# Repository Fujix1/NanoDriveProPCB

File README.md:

# NanoDriveProPCB
This is a PCB design repository for NanoDrive PRO

<br />この 作品 は <a rel="license" href="http://creativecommons.org/licenses/by-nc-sa/4.0/">クリエイティブ・コモンズ 表示 - 非営利 - 継承 4.0 国際 ライセンス</a>の下に提供されています。

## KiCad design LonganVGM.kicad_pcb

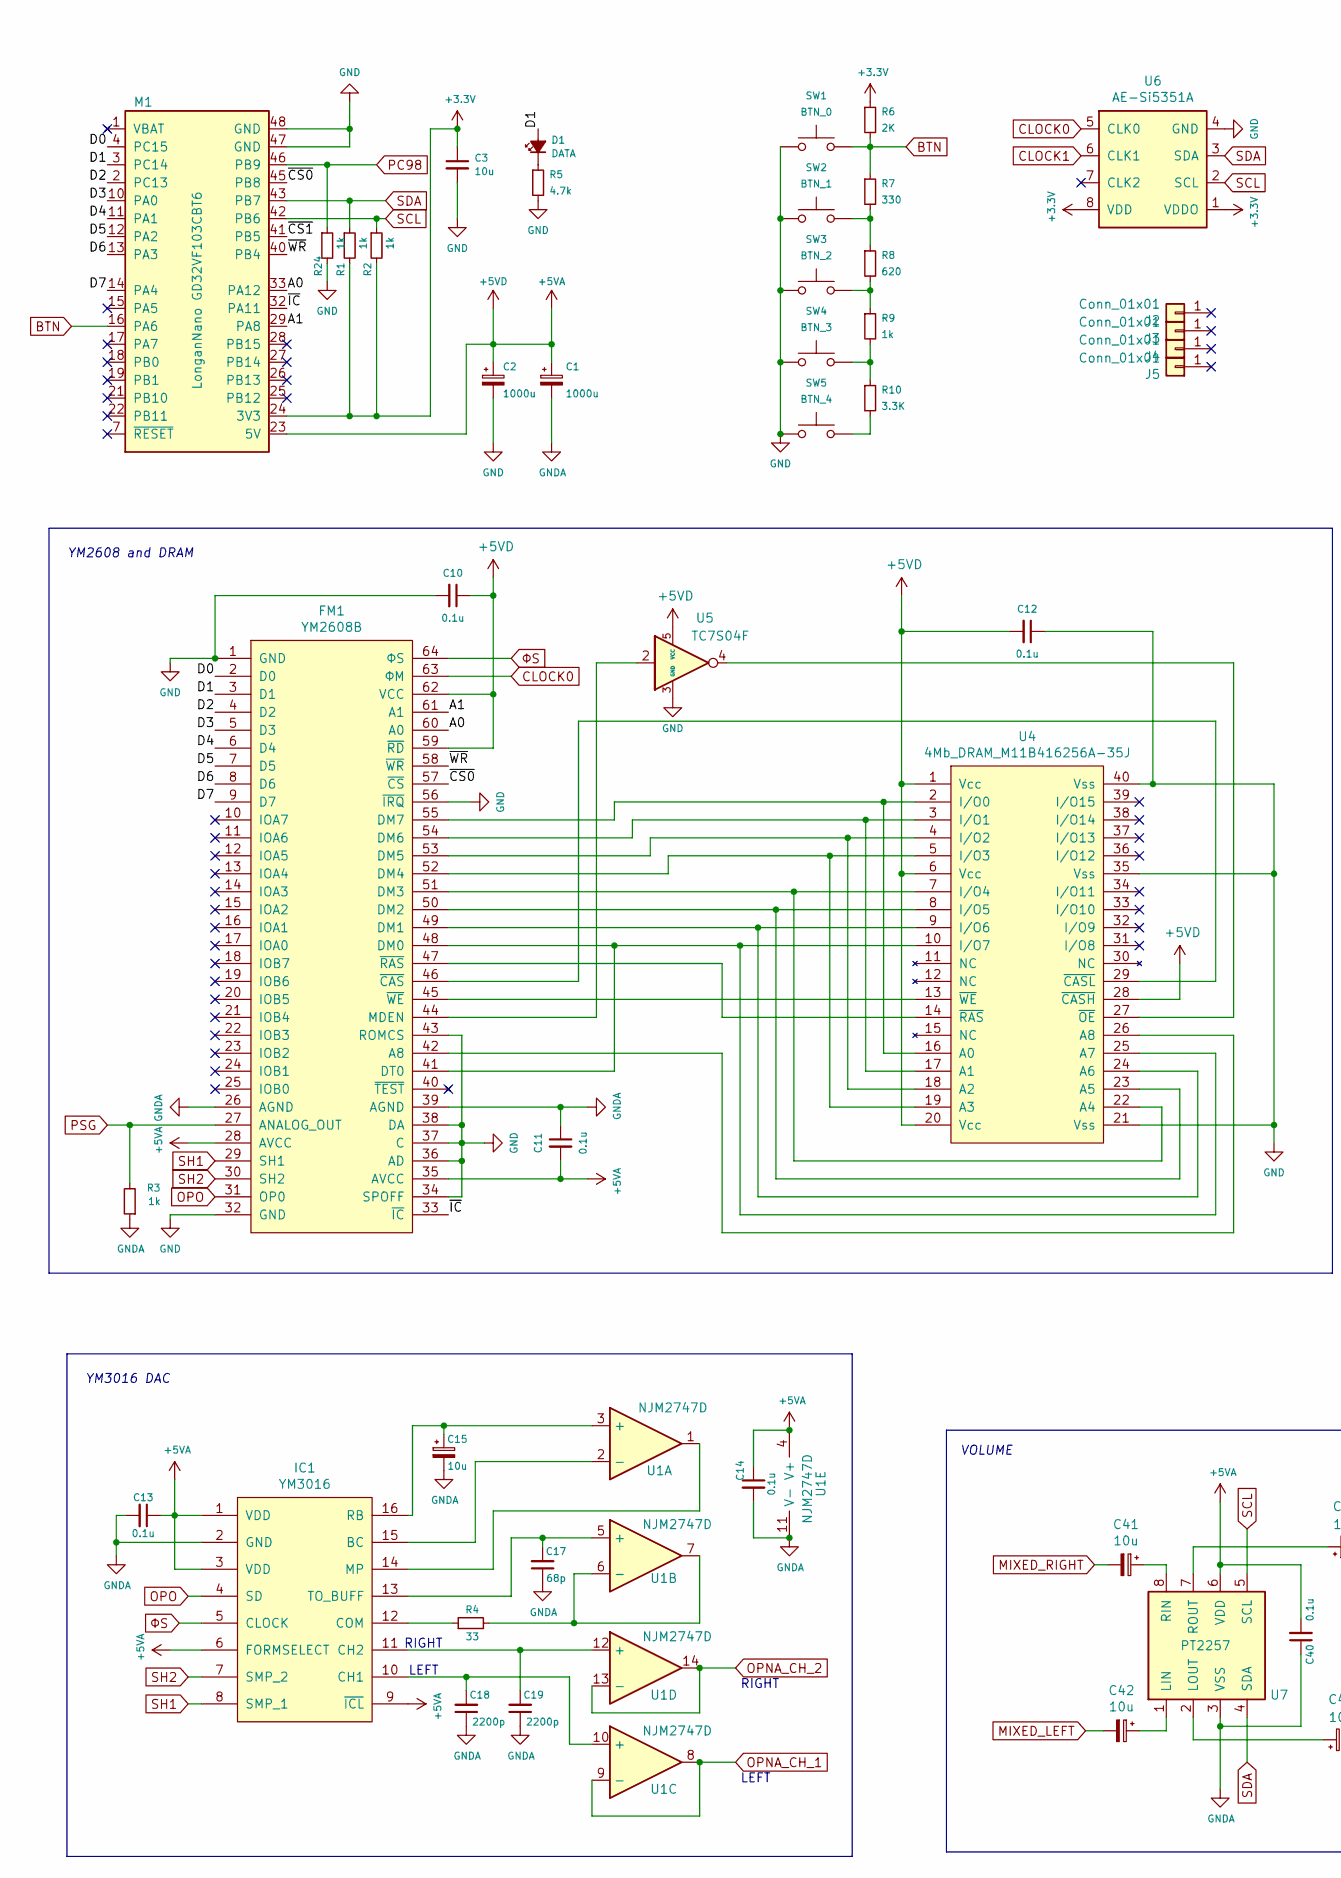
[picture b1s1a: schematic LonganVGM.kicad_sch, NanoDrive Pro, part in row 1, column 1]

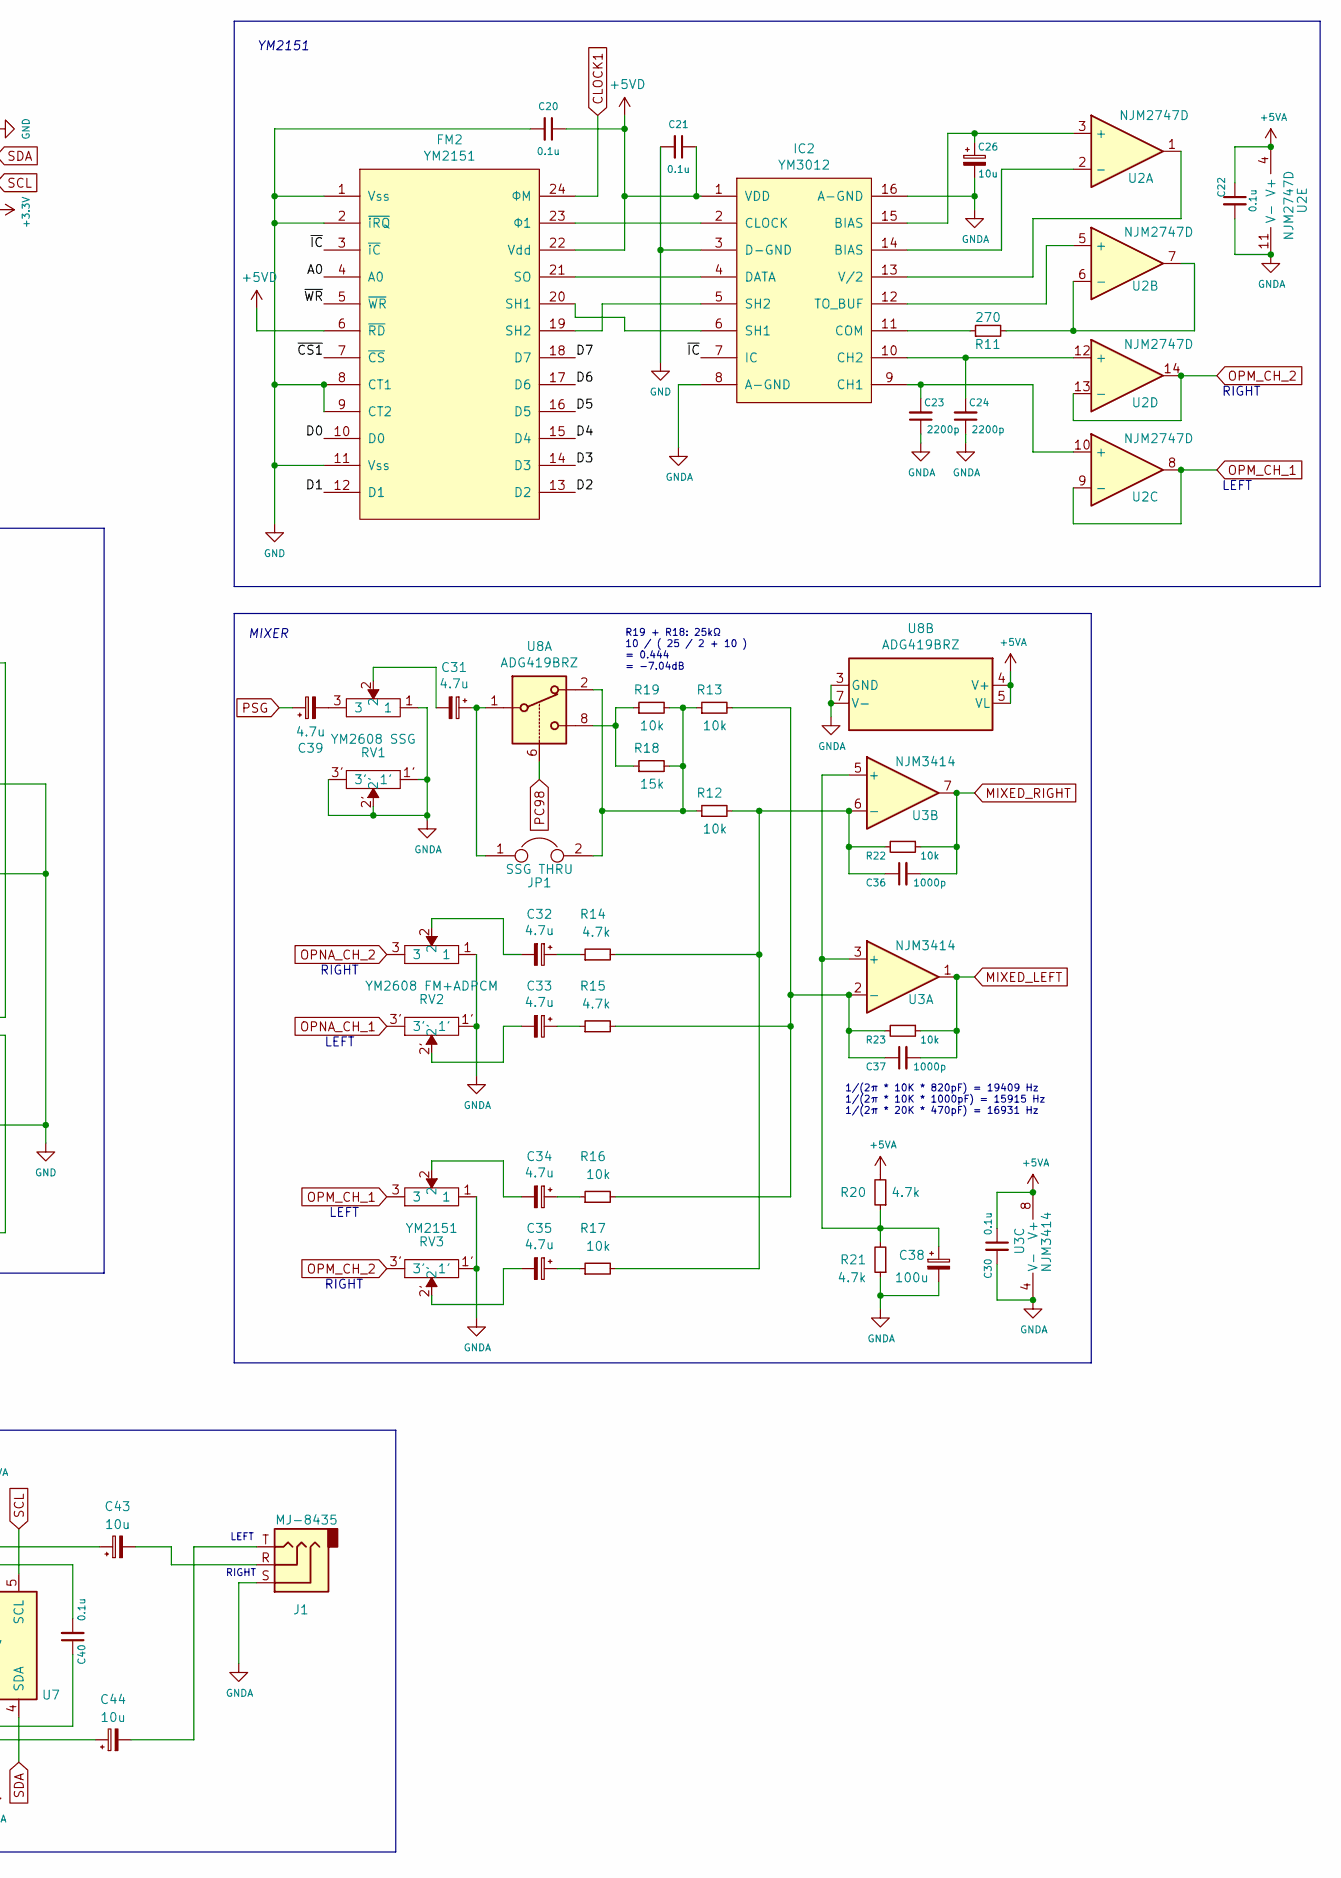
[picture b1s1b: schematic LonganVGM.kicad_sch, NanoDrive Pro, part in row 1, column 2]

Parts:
C1, C2: 1000u; CP_Radial_D8.0mm_P3.50mm
C3, C15, C26, C41, C42, C43, C44: 10u; CP_Radial_D5.0mm_P2.00mm
C10, C11, C12, C13, C14, C20, C21, C22, C30, C40: 0.1u; C_Disc_D4.3mm_W1.9mm_P5.00mm
C17: 68p; C_Disc_D4.3mm_W1.9mm_P5.00mm
C18, C19, C23, C24: 2200p; C_Disc_D4.3mm_W1.9mm_P5.00mm
C31, C32, C33, C34, C35, C39: 4.7u; CP_Radial_D5.0mm_P2.00mm
C36, C37: 1000p; C_Disc_D4.3mm_W1.9mm_P5.00mm
C38: 100u; CP_Radial_D6.3mm_P2.50mm
D1: DATA; LED_Rectangular_W5.0mm_H2.0mm
FM1: YM2608B; SDIP-64
FM2: YM2151; DIP-24_W15.24mm_Socket
IC1: YM3016; DIP-16_W7.62mm_Socket
IC2: YM3012; DIP-16_W7.62mm_Socket
J1: MJ-8435; MJ8435
J2, J3, J4, J5: Conn_01x01; hole
JP1: SSG THRU; PinHeader_1x02_P2.54mm_Vertical
M1: LonganNano GD32VF103CBT6; LonganNano
R1, R2, R3, R9, R24: 1k; R_Axial_DIN0207_L6.3mm_D2.5mm_P7.62mm_Horizontal
R4: 33; R_Axial_DIN0207_L6.3mm_D2.5mm_P7.62mm_Horizontal
R5, R14, R15, R20, R21: 4.7k; R_Axial_DIN0207_L6.3mm_D2.5mm_P7.62mm_Horizontal
R6: 2K; R_Axial_DIN0207_L6.3mm_D2.5mm_P7.62mm_Horizontal
R7: 330; R_Axial_DIN0207_L6.3mm_D2.5mm_P7.62mm_Horizontal
R8: 620; R_Axial_DIN0207_L6.3mm_D2.5mm_P7.62mm_Horizontal
R10: 3.3K; R_Axial_DIN0207_L6.3mm_D2.5mm_P7.62mm_Horizontal
R11: 270; R_Axial_DIN0207_L6.3mm_D2.5mm_P7.62mm_Horizontal
R12, R13, R16, R17, R19, R22, R23: 10k; R_Axial_DIN0207_L6.3mm_D2.5mm_P7.62mm_Horizontal
R18: 15k; R_Axial_DIN0207_L6.3mm_D2.5mm_P7.62mm_Horizontal
RV1: YM2608 SSG; RK12L
RV2: YM2608 FM+ADPCM; RK12L
RV3: YM2151; RK12L
SW1: BTN_0; SW_PUSH_6mm_H4.3mm
SW2: BTN_1; SW_PUSH_6mm_H4.3mm
SW3: BTN_2; SW_PUSH_6mm_H4.3mm
SW4: BTN_3; SW_PUSH_6mm_H4.3mm
SW5: BTN_4; SW_PUSH_6mm_H4.3mm
U1, U2: NJM2747D; DIP-14_W7.62mm_Socket
U3: NJM3414; DIP-8_W7.62mm_Socket
U4: 4Mb_DRAM_M11B416256A-35J; SOP-40
U5: TC7S04F; SOT-23-5_HandSoldering
U6: AE-Si5351A; DIP-8_W7.62mm_Socket
U7: PT2257; DIP-8_W7.62mm_Socket
U8: ADG419BRZ; SO-8_3.9x4.9mm_P1.27mm_handsolder

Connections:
+3V3: C3.1, M1.24 (3V3), R1.2, R2.2, R6.1, U6.1 (VDDO), U6.8 (VDD)
+5VA: C1.1, C2.1, C10.1, C11.2, C12.2, C13.1, C14.1, C20.1, C21.1, C22.1, C30.1, C40.2, FM1.28 (AVCC), FM1.35 (AVCC), FM1.59 (~RD), FM1.62 (VCC), FM2.6 (~RD), FM2.22 (Vdd), IC1.1 (VDD), IC1.3 (VDD), IC1.6 (FORMSELECT), IC1.9 (~ICL), IC2.1 (VDD), M1.23 (5V), R20.2, U1.4 (V+), U2.4 (V+), U3.8 (V+), U4.1 (Vcc), U4.6 (Vcc), U4.20 (Vcc), U4.28 (~CASH), U5.5 (VCC), U7.6 (VDD), U8.4 (V+), U8.5 (VL)
/A0: FM1.60 (A0), FM2.4 (A0), M1.33 (PA12)
/A1: FM1.61 (A1), M1.29 (PA8)
/D0: FM1.2 (D0), FM2.10 (D0), M1.4 (PC15)
/D1: D1.2 (A), FM1.3 (D1), FM2.12 (D1), M1.3 (PC14)
/D2: FM1.4 (D2), FM2.13 (D2), M1.2 (PC13)
/D3: FM1.5 (D3), FM2.14 (D3), M1.10 (PA0)
/D4: FM1.6 (D4), FM2.15 (D4), M1.11 (PA1)
/D5: FM1.7 (D5), FM2.16 (D5), M1.12 (PA2)
/D6: FM1.8 (D6), FM2.17 (D6), M1.13 (PA3)
/D7: FM1.9 (D7), FM2.18 (D7), M1.14 (PA4)
/~CS0: FM1.57 (~CS), M1.45 (PB8)
/~CS1: FM2.7 (~CS), M1.41 (PB5)
/~IC: FM1.33 (~IC), FM2.3 (~iC), IC2.7 (IC), M1.32 (PA11)
/~WR: FM1.58 (~WR), FM2.5 (~WR), M1.40 (PB4)
BTN: M1.16 (PA6), R6.2, R7.1, SW1.2
CLOCK0: FM1.63 (ΦM), U6.5 (CLK0)
CLOCK1: FM2.24 (ΦM), U6.6 (CLK1)
MIXED_LEFT: C37.2, C42.2, R23.1, U3.1
MIXED_RIGHT: C36.2, C41.2, R22.1, U3.7
unnamed: C15.1, IC1.16 (RB), U1.3 (+)
unnamed: C17.2, IC1.13 (TO_BUFF), U1.5 (+)
unnamed: C18.2, IC1.10 (CH1), U1.10 (+)
unnamed: C19.2, IC1.11 (CH2), U1.12 (+)
unnamed: C23.2, IC2.9 (CH1), U2.10 (+)
unnamed: C24.2, IC2.10 (CH2), U2.12 (+)
unnamed: C26.1, IC2.15 (BIAS), U2.3 (+)
unnamed: C31.1, JP1.1, U8.1
unnamed: C31.2, RV1.2
unnamed: C32.1, R14.1
unnamed: C32.2, RV2.2
unnamed: C33.1, R15.1
unnamed: C33.2, RV2.2'
unnamed: C34.1, R16.1
unnamed: C34.2, RV3.2
unnamed: C35.1, R17.1
unnamed: C35.2, RV3.2'
unnamed: C36.1, R12.2, R14.2, R17.2, R22.2, U3.6 (-)
unnamed: C37.1, R13.2, R15.2, R16.2, R23.2, U3.2 (-)
unnamed: C38.1, R20.1, R21.2, U3.3 (+), U3.5 (+)
unnamed: C39.2, RV1.3
unnamed: C41.1, U7.8 (RIN)
unnamed: C42.1, U7.1 (LIN)
unnamed: C43.1, U7.7 (ROUT)
unnamed: C43.2, J1.R
unnamed: C44.1, U7.2 (LOUT)
unnamed: C44.2, J1.T
unnamed: D1.1 (K), R5.1
unnamed: FM1.41 (DT0), FM1.48 (DM0), U4.10 (I/O7), U4.25 (A7)
unnamed: FM1.42 (A8), U4.26 (A8)
unnamed: FM1.44 (MDEN), U5.2
unnamed: FM1.45 (~WE), U4.13 (~WE)
unnamed: FM1.46 (~CAS), U4.29 (~CASL)
unnamed: FM1.47 (~RAS), U4.14 (~RAS)
unnamed: FM1.49 (DM1), U4.9 (I/O6), U4.24 (A6)
unnamed: FM1.50 (DM2), U4.8 (I/O5), U4.23 (A5)
unnamed: FM1.51 (DM3), U4.7 (I/O4), U4.22 (A4)
unnamed: FM1.52 (DM4), U4.5 (I/O3), U4.19 (A3)
unnamed: FM1.53 (DM5), U4.4 (I/O2), U4.18 (A2)
unnamed: FM1.54 (DM6), U4.3 (I/O1), U4.17 (A1)
unnamed: FM1.55 (DM7), U4.2 (I/O0), U4.16 (A0)
unnamed: FM2.19 (SH2), IC2.5 (SH2)
unnamed: FM2.20 (SH1), IC2.6 (SH1)
unnamed: FM2.21 (SO), IC2.4 (DATA)
unnamed: FM2.23 (Φ1), IC2.2 (CLOCK)
unnamed: IC1.12 (COM), R4.1
unnamed: IC1.14 (MP), U1.1
unnamed: IC1.15 (BC), U1.2 (-)
unnamed: IC2.11 (COM), R11.1
unnamed: IC2.12 (TO_BUF), U2.5 (+)
unnamed: IC2.13 (V/2), U2.1
unnamed: IC2.14 (BIAS), U2.2 (-)
unnamed: JP1.2, R12.1, R13.1, R18.2, R19.2, U8.2
unnamed: R4.2, U1.6 (-), U1.7
unnamed: R7.2, R8.1, SW2.2
unnamed: R8.2, R9.1, SW3.2
unnamed: R9.2, R10.1, SW4.2
unnamed: R10.2, SW5.2
unnamed: R11.2, U2.6 (-), U2.7
unnamed: R18.1, R19.1, U8.8
unnamed: U4.27 (~OE), U5.4
OPM_CH_1: RV3.3, U2.8, U2.9 (-)
OPM_CH_2: RV3.3', U2.13 (-), U2.14
OPNA_CH_1: RV2.3', U1.8, U1.9 (-)
OPNA_CH_2: RV2.3, U1.13 (-), U1.14
OPO: FM1.31 (OP0), IC1.4 (SD)
PC98: M1.46 (PB9), R24.1, U8.6
PSG: C39.1, FM1.27 (ANALOG_OUT), R3.2
SCL: M1.42 (PB6), R2.1, U6.2 (SCL), U7.5 (SCL)
SDA: M1.43 (PB7), R1.1, U6.3 (SDA), U7.4 (SDA)
SH1: FM1.29 (SH1), IC1.8 (SMP_1)
SH2: FM1.30 (SH2), IC1.7 (SMP_2)
ΦS: FM1.64 (ΦS), IC1.5 (CLOCK)

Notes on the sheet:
RIGHT
LEFT
R19 + R18: 25kΩ 10 / ( 25 / 2 + 10 ) = 0.444 = -7.04dB
1/(2π * 10K * 820pF) = 19409 Hz 1/(2π * 10K * 1000pF) = 15915 Hz 1/(2π * 20K * 470pF) = 16931 Hz
YM2608 and DRAM
RIGHT
YM2151
YM3016 DAC
MIXER
VOLUME

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
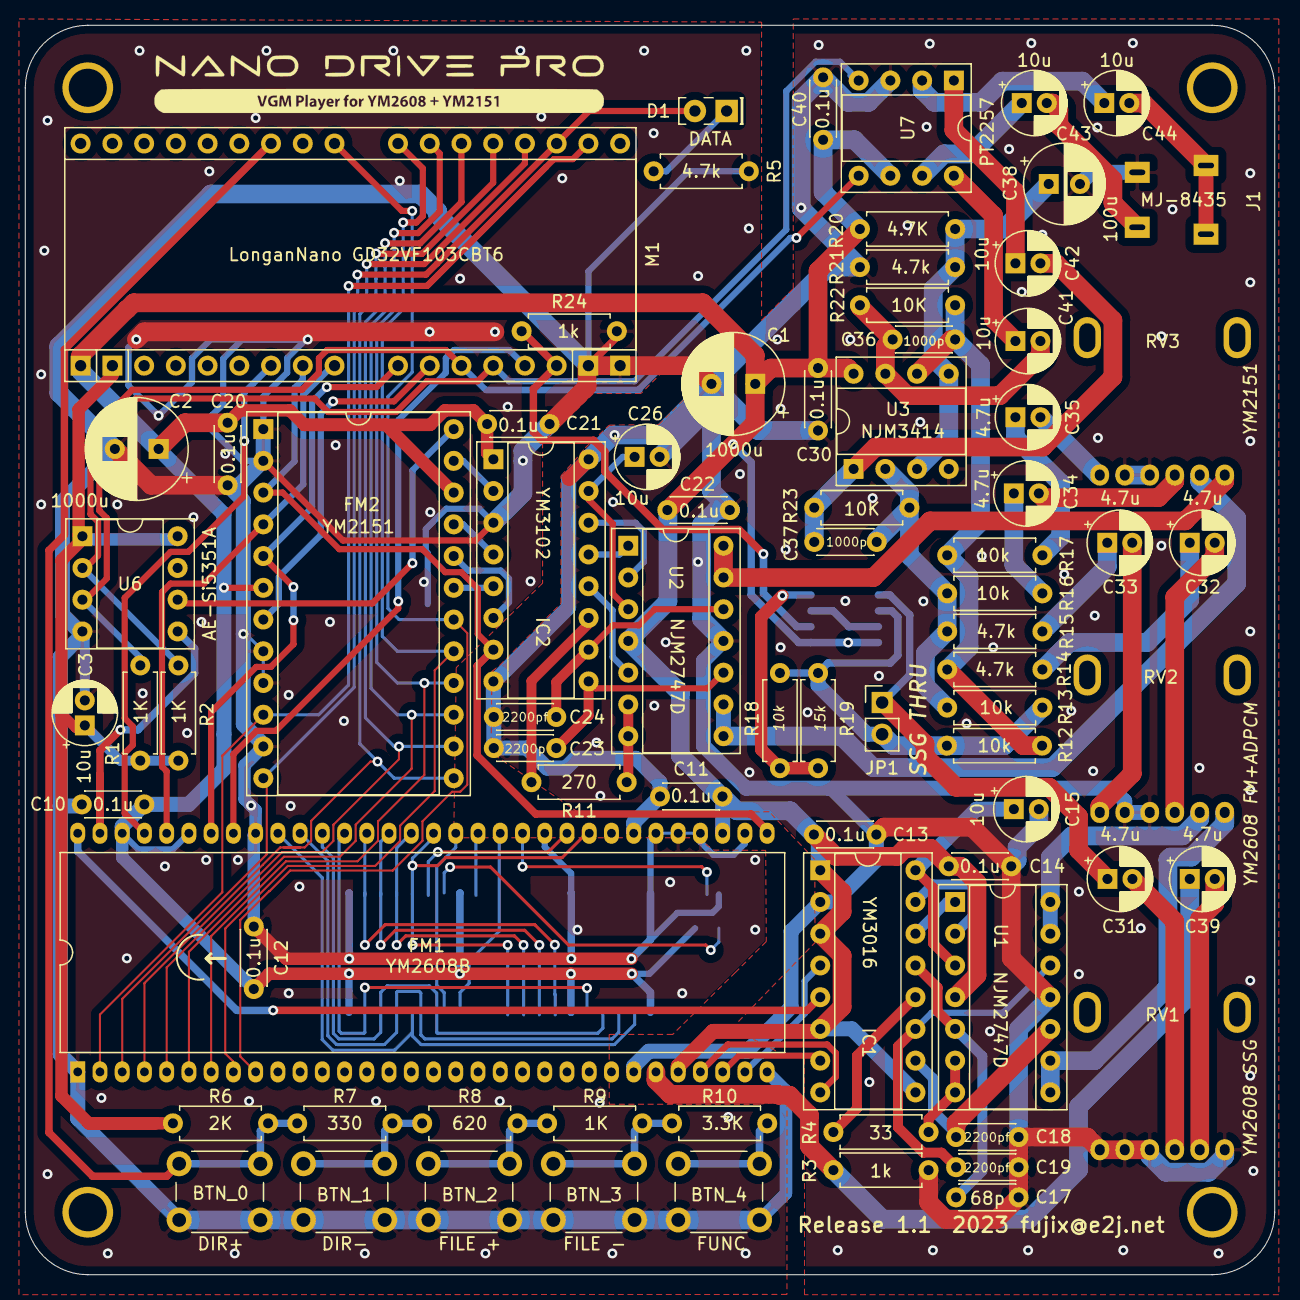
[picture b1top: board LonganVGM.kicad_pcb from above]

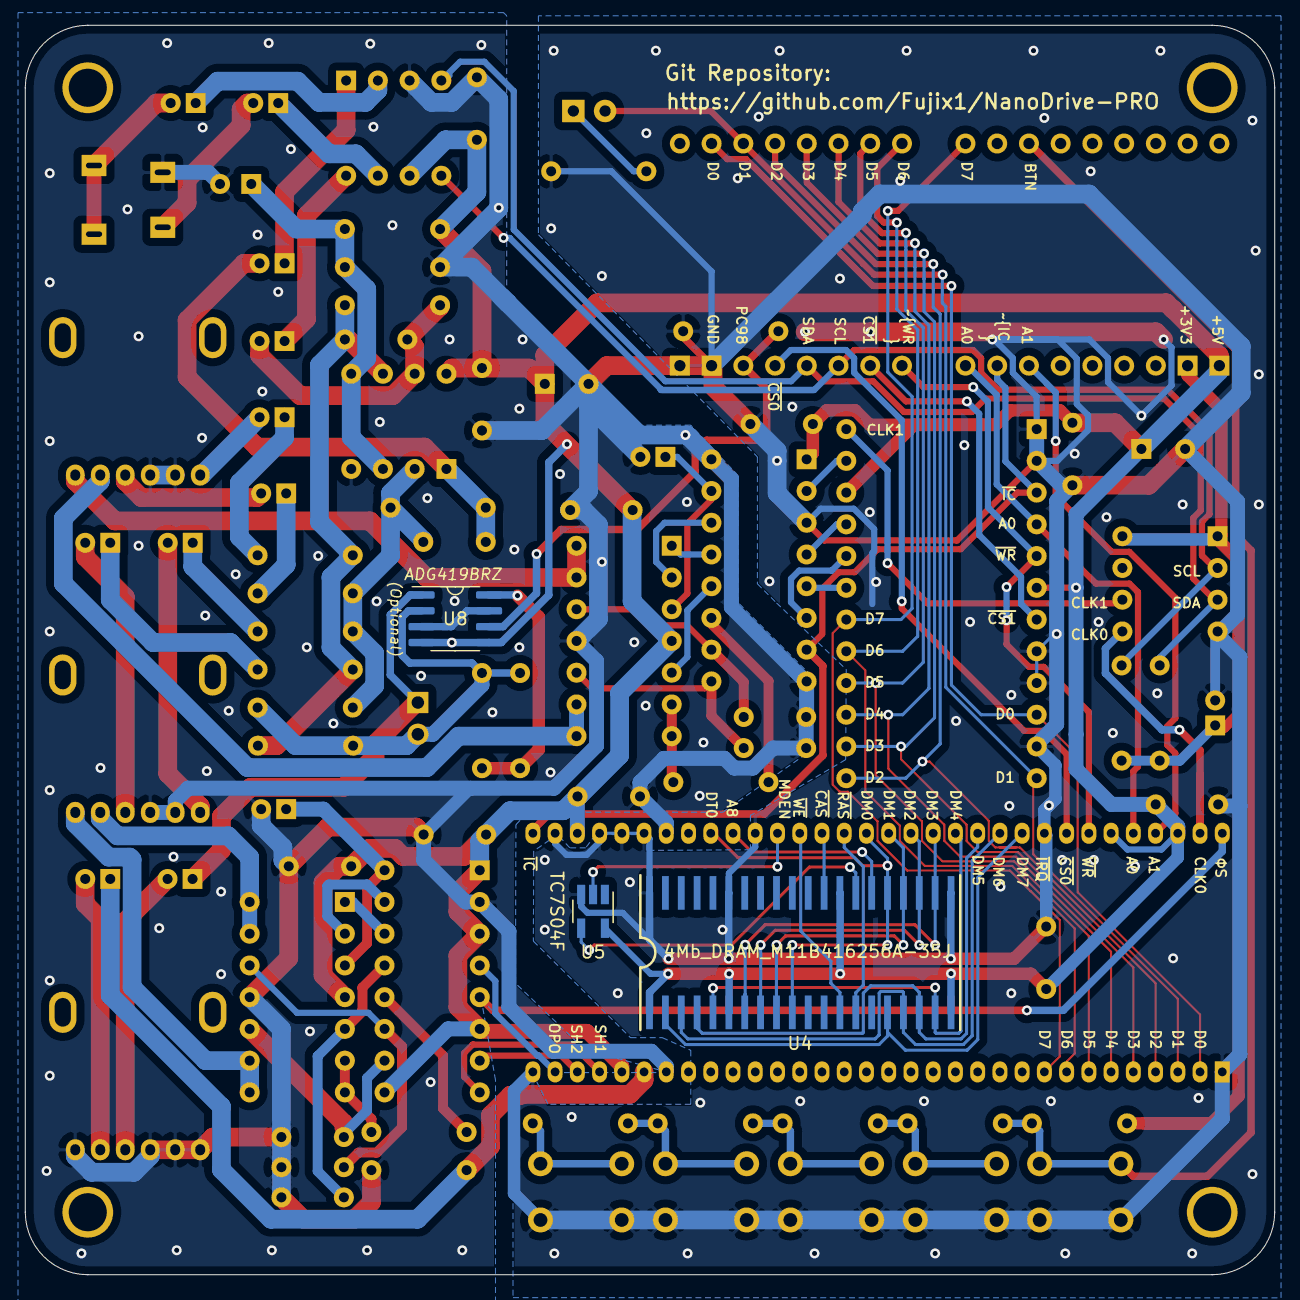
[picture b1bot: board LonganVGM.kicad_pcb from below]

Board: 2 copper layers, 100.0 x 100.0 mm, 85 parts (3 on the bottom side), 95 nets.

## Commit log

2023-03-27 Initial files
2023-03-27 LICENSE

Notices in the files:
README.md:
CC BY-NC-SA 4.0
